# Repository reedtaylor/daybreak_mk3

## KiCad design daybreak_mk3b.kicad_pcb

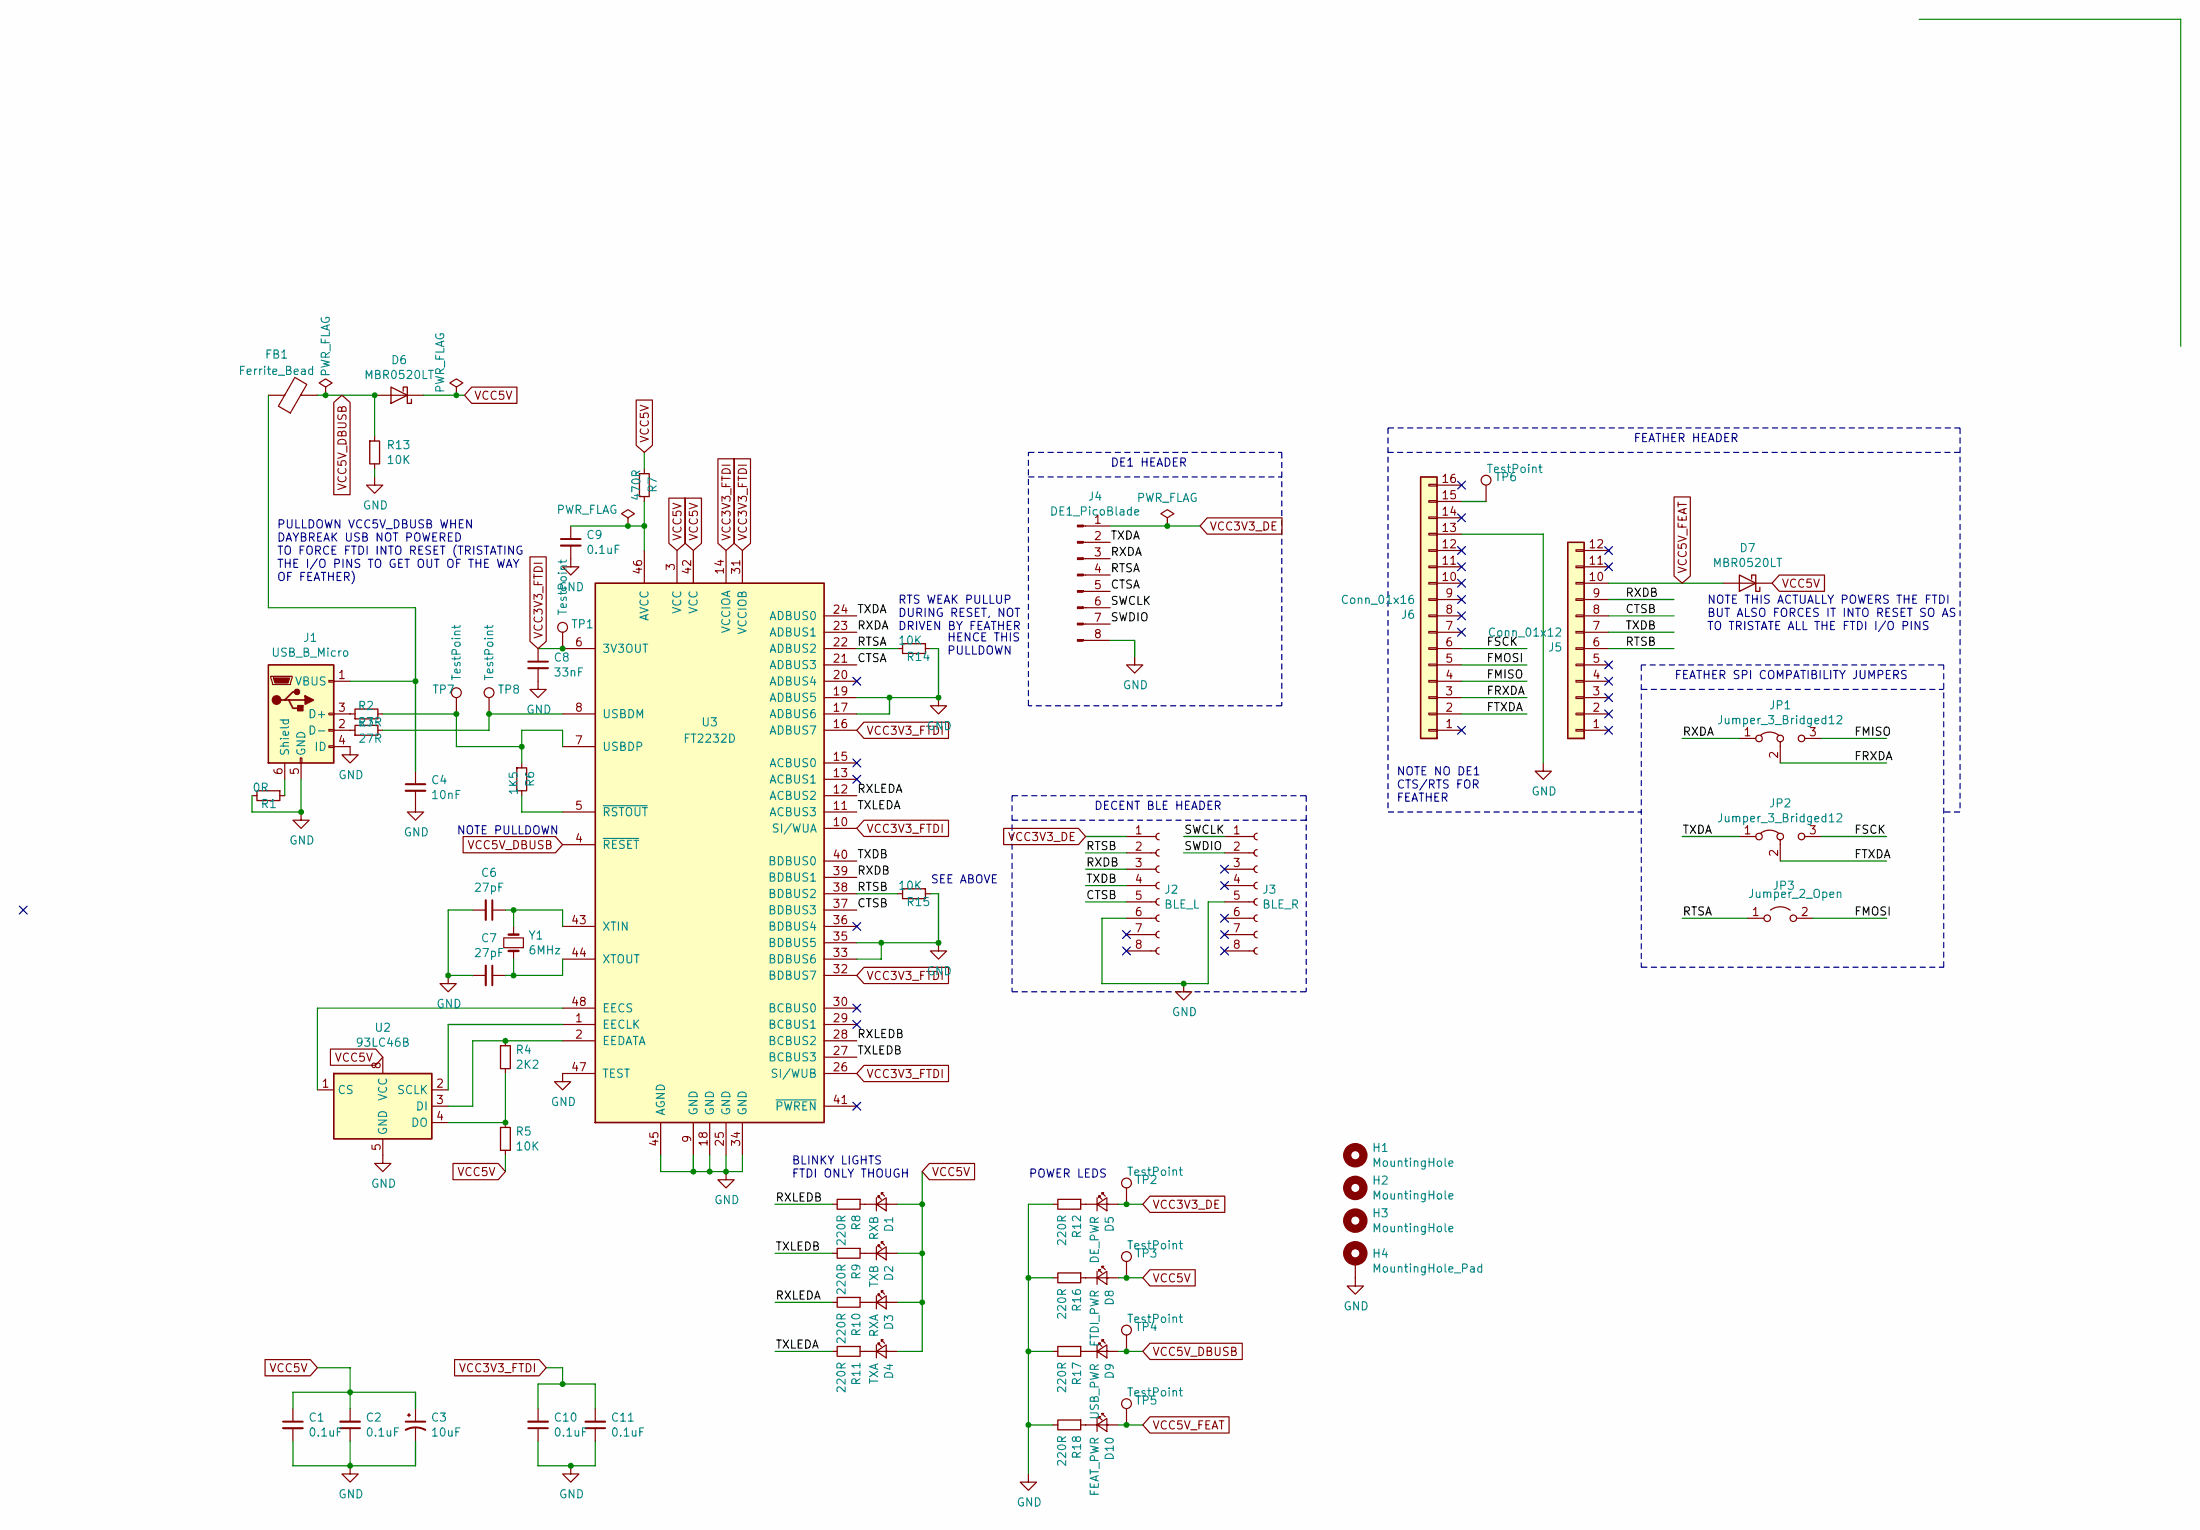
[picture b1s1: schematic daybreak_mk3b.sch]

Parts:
C1, C2, C9, C10, C11: 0.1uF; C_0603_1608Metric
C3: 10uF; C_0603_1608Metric
C4: 10nF; C_0603_1608Metric
C6, C7: 27pF; C_0603_1608Metric
C8: 33nF; C_0603_1608Metric
D1: RXB; LED_0603_1608Metric
D2: TXB; LED_0603_1608Metric
D3: RXA; LED_0603_1608Metric
D4: TXA; LED_0603_1608Metric
D5: DE_PWR; LED_0603_1608Metric
D6, D7: MBR0520LT; D_SOD-123
D8: FTDI_PWR; LED_0603_1608Metric
D9: USB_PWR; LED_0603_1608Metric
D10: FEAT_PWR; LED_0603_1608Metric
FB1: Ferrite_Bead; INDC2012X110N
H1, H2, H3: MountingHole; MountingHole_3.2mm_M3
H4: MountingHole_Pad; MountingHole_3.2mm_M3_Pad
J1: USB_B_Micro; USB_Micro-B_Molex-105133-0001
J2: BLE_L; PinSocket_1x08_P2.54mm_Vertical
J3: BLE_R; PinSocket_1x08_P2.54mm_Vertical
J4: DE1_PicoBlade; Molex_PicoBlade_53047-0810_1x08_P1.25mm_Vertical
J5: Conn_01x12; PinSocket_1x12_P2.54mm_Vertical
J6: Conn_01x16; PinSocket_1x16_P2.54mm_Vertical
JP1, JP2: Jumper_3_Bridged12; SolderJumper-3_P1.3mm_Bridged2Bar12_Pad1.0x1.5mm
JP3: Jumper_2_Open; SolderJumper-2_P1.3mm_Open_Pad1.0x1.5mm
R1: 0R; R_0603_1608Metric
R2, R3: 27R; R_0603_1608Metric
R4: 2K2; R_0603_1608Metric
R5, R13, R14, R15: 10K; R_0603_1608Metric
R6: 1K5; R_0603_1608Metric
R7: 470R; R_0603_1608Metric
R8, R9, R10, R11, R12, R16, R17, R18: 220R; R_0603_1608Metric
TP1, TP2, TP3, TP4, TP5, TP6, TP7, TP8: TestPoint; TestPoint_THTPad_D2.0mm_Drill1.0mm
U2: 93LC46B; SOIC-8-1EP_3.9x4.9mm_P1.27mm_EP2.29x3mm
U3: FT2232D; LQFP-48_7x7mm_P0.5mm
Y1: 6MHz; Crystal_SMD_SeikoEpson_MA505-2Pin_12.7x5.1mm

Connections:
/CTSA: J4.5, U3.21 (ADBUS3)
/CTSB: J2.5, J5.8, U3.37 (BDBUS3)
/FMISO: J6.4, JP1.3 (B)
/FMOSI: J6.5, JP3.2 (B)
/FRXDA: J6.3, JP1.2 (C)
/FSCK: J6.6, JP2.3 (B)
/FTXDA: J6.2, JP2.2 (C)
/RTSA: J4.4, JP3.1 (A), R14.2, U3.22 (ADBUS2)
/RTSB: J2.2, J5.6, R15.2, U3.38 (BDBUS2)
/RXDA: J4.3, JP1.1 (A), U3.23 (ADBUS1)
/RXDB: J2.3, J5.9, U3.39 (BDBUS1)
/RXLEDA: R10.2, U3.12 (ACBUS2)
/RXLEDB: R8.2, U3.28 (BCBUS2)
/SWCLK: J3.1, J4.6
/SWDIO: J3.2, J4.7
/TXDA: J4.2, JP2.1 (A), U3.24 (ADBUS0)
/TXDB: J2.4, J5.7, U3.40 (BDBUS0)
/TXLEDA: R11.2, U3.11 (ACBUS3)
/TXLEDB: R9.2, U3.27 (BCBUS3)
GND: C1.2, C2.1, C3.2, C4.2, C6.2, C7.2, C8.2, C9.2, C10.1, C11.1, H4.1, J1.4 (ID), J1.5 (GND), J2.6, J3.5, J4.8, J6.13, R1.2, R12.2, R13.2, R14.1, R15.1, R16.2, R17.2, R18.2, U2.5 (GND), U3.9 (GND), U3.17 (ADBUS6), U3.18 (GND), U3.19 (ADBUS5), U3.25 (GND), U3.33 (BDBUS6), U3.34 (GND), U3.35 (BDBUS5), U3.45 (AGND), U3.47 (TEST)
unnamed: C4.1, FB1.1, J1.1 (VBUS)
unnamed: C6.1, U3.43 (XTIN), Y1.2
unnamed: C7.1, U3.44 (XTOUT), Y1.1
unnamed: C9.1, R7.2, U3.46 (AVCC)
unnamed: D1.1 (K), R8.1
unnamed: D2.1 (K), R9.1
unnamed: D3.1 (K), R10.1
unnamed: D4.1 (K), R11.1
unnamed: D5.1 (K), R12.1
unnamed: D8.1 (K), R16.1
unnamed: D9.1 (K), R17.1
unnamed: D10.1 (K), R18.1
unnamed: J1.2 (D-), R3.1
unnamed: J1.3 (D+), R2.1
unnamed: J1.6 (Shield), R1.1
unnamed: J6.15, TP6.1
unnamed: R2.2, R6.1, TP7.1, U3.7 (USBDP)
unnamed: R3.2, TP8.1, U3.8 (USBDM)
unnamed: R4.1, U2.3 (DI), U3.2 (EEDATA)
unnamed: R4.2, R5.1, U2.4 (DO)
unnamed: R6.2, U3.5 (~RSTOUT)
unnamed: U2.1 (CS), U3.48 (EECS)
unnamed: U2.2 (SCLK), U3.1 (EECLK)
VCC3V3_DE: D5.2 (A), J2.1, J4.1, TP2.1
VCC3V3_FTDI: C8.1, C10.2, C11.2, TP1.1, U3.6 (3V3OUT), U3.10 (SI/WUA), U3.14 (VCCIOA), U3.16 (ADBUS7), U3.26 (SI/WUB), U3.31 (VCCIOB), U3.32 (BDBUS7)
VCC5V: C1.1, C2.2, C3.1, D1.2 (A), D2.2 (A), D3.2 (A), D4.2 (A), D6.1 (K), D7.1 (K), D8.2 (A), R5.2, R7.1, TP3.1, U2.8 (VCC), U3.3 (VCC), U3.42 (VCC)
VCC5V_DBUSB: D6.2 (A), D9.2 (A), FB1.2, R13.1, TP4.1, U3.4 (~RESET)
VCC5V_FEAT: D7.2 (A), D10.2 (A), J5.10, TP5.1

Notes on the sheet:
PULLDOWN VCC5V_DBUSB WHEN DAYBREAK USB NOT POWERED TO FORCE FTDI INTO RESET (TRISTATING THE I/O PINS TO GET OUT OF THE WAY OF FEATHER)
NOTE PULLDOWN
NOTE THIS ACTUALLY POWERS THE FTDI BUT ALSO FORCES IT INTO RESET SO AS TO TRISTATE ALL THE FTDI I/O PINS
DE1 HEADER
FEATHER HEADER
BLINKY LIGHTS FTDI ONLY THOUGH
DECENT BLE HEADER
NOTE NO DE1 CTS/RTS FOR FEATHER
RTS WEAK PULLUP DURING RESET, NOT DRIVEN BY FEATHER
HENCE THIS PULLDOWN
SEE ABOVE
POWER LEDS
FEATHER SPI COMPATIBILITY JUMPERS

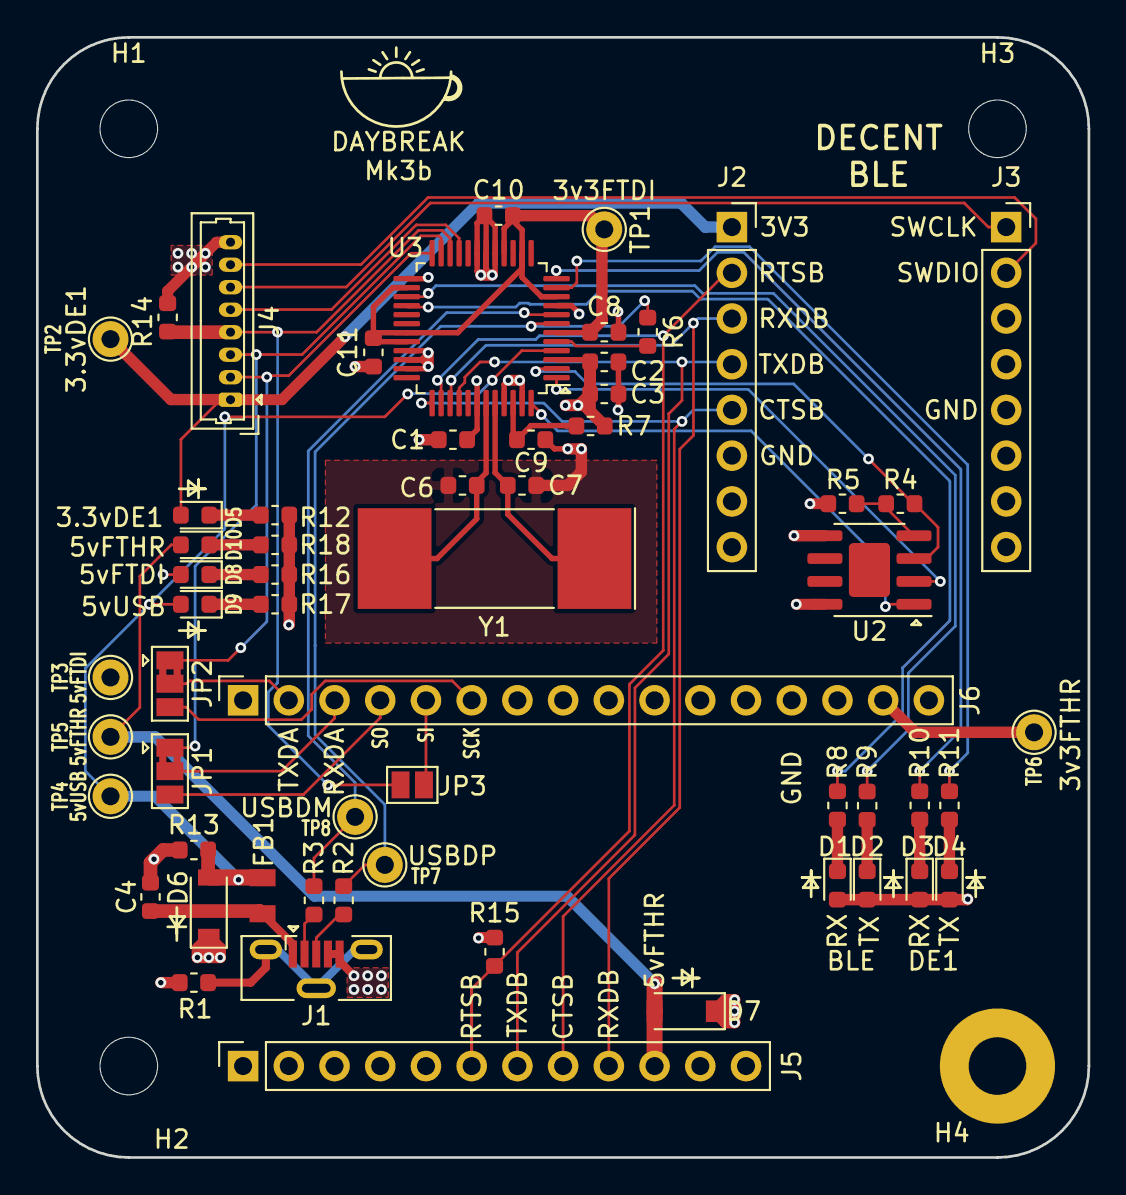
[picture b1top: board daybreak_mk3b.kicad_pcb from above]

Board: 4 copper layers, 58.4 x 62.2 mm, 63 parts (0 on the bottom side), 48 nets.

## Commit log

2020-01-24 3d model
